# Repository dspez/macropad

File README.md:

Files sent to JLCPCB for macropad production - tested and functional

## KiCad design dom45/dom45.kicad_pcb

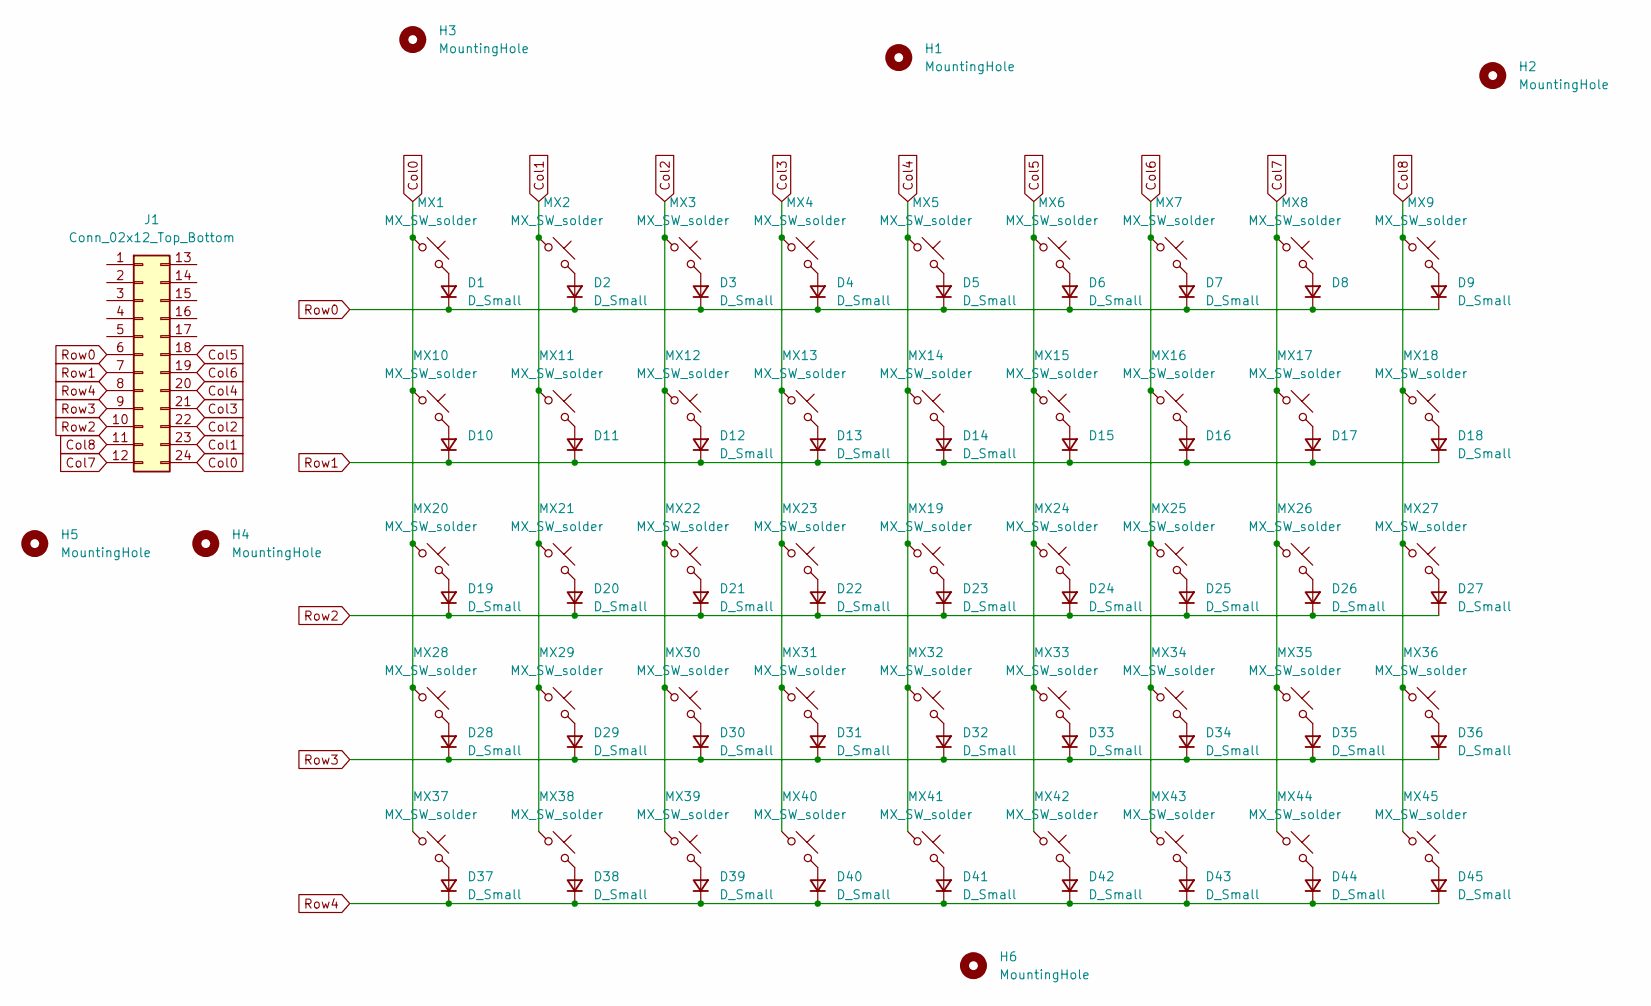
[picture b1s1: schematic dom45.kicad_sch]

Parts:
D1, D2, D3, D4, D5, D6, D7, D8, D9, D10, D11, D12, D13, D14, D15, D16, D17, D18, D19, D20, D21, D22, D23, D24, D25, D26, D27, D28, D29, D30, D31, D32, D33, D34, D35, D36, D37, D38, D39, D40, D41, D42, D43, D44, D45: D_Small; D_SOD-123; LCSC C81598
H1, H2, H3, H4, H5, H6: MountingHole; MountingHole_3.2mm_M3_DIN965_Pad_TopBottom
J1: Conn_02x12_Top_Bottom; ProMicro_USBup
MX1, MX2, MX3, MX4, MX5, MX6, MX7, MX8, MX9, MX10, MX11, MX12, MX13, MX14, MX15, MX16, MX17, MX18, MX19, MX20, MX21, MX22, MX23, MX24, MX25, MX26, MX27, MX28, MX29, MX30, MX31, MX32, MX33, MX34, MX35, MX36, MX37, MX38, MX39, MX40, MX41, MX42, MX43, MX44, MX45: MX_SW_solder; SW_MX_1u

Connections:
Col0: J1.24, MX1.1, MX10.1, MX20.1, MX28.1, MX37.1
Col1: J1.23, MX2.1, MX11.1, MX21.1, MX29.1, MX38.1
Col2: J1.22, MX3.1, MX12.1, MX22.1, MX30.1, MX39.1
Col3: J1.21, MX4.1, MX13.1, MX23.1, MX31.1, MX40.1
Col4: J1.20, MX5.1, MX14.1, MX19.1, MX32.1, MX41.1
Col5: J1.18, MX6.1, MX15.1, MX24.1, MX33.1, MX42.1
Col6: J1.19, MX7.1, MX16.1, MX25.1, MX34.1, MX43.1
Col7: J1.12, MX8.1, MX17.1, MX26.1, MX35.1, MX44.1
Col8: J1.11, MX9.1, MX18.1, MX27.1, MX36.1, MX45.1
unnamed: D1.2 (A), MX1.2
unnamed: D2.2 (A), MX2.2
unnamed: D3.2 (A), MX3.2
unnamed: D4.2 (A), MX4.2
unnamed: D5.2 (A), MX5.2
unnamed: D6.2 (A), MX6.2
unnamed: D7.2 (A), MX7.2
unnamed: D8.2 (A), MX8.2
unnamed: D9.2 (A), MX9.2
unnamed: D10.2 (A), MX10.2
unnamed: D11.2 (A), MX11.2
unnamed: D12.2 (A), MX12.2
unnamed: D13.2 (A), MX13.2
unnamed: D14.2 (A), MX14.2
unnamed: D15.2 (A), MX15.2
unnamed: D16.2 (A), MX16.2
unnamed: D17.2 (A), MX17.2
unnamed: D18.2 (A), MX18.2
unnamed: D19.2 (A), MX20.2
unnamed: D20.2 (A), MX21.2
unnamed: D21.2 (A), MX22.2
unnamed: D22.2 (A), MX23.2
unnamed: D23.2 (A), MX19.2
unnamed: D24.2 (A), MX24.2
unnamed: D25.2 (A), MX25.2
unnamed: D26.2 (A), MX26.2
unnamed: D27.2 (A), MX27.2
unnamed: D28.2 (A), MX28.2
unnamed: D29.2 (A), MX29.2
unnamed: D30.2 (A), MX30.2
unnamed: D31.2 (A), MX31.2
unnamed: D32.2 (A), MX32.2
unnamed: D33.2 (A), MX33.2
unnamed: D34.2 (A), MX34.2
unnamed: D35.2 (A), MX35.2
unnamed: D36.2 (A), MX36.2
unnamed: D37.2 (A), MX37.2
unnamed: D38.2 (A), MX38.2
unnamed: D39.2 (A), MX39.2
unnamed: D40.2 (A), MX40.2
unnamed: D41.2 (A), MX41.2
unnamed: D42.2 (A), MX42.2
unnamed: D43.2 (A), MX43.2
unnamed: D44.2 (A), MX44.2
unnamed: D45.2 (A), MX45.2
Row0: D1.1 (K), D2.1 (K), D3.1 (K), D4.1 (K), D5.1 (K), D6.1 (K), D7.1 (K), D8.1 (K), D9.1 (K), J1.6
Row1: D10.1 (K), D11.1 (K), D12.1 (K), D13.1 (K), D14.1 (K), D15.1 (K), D16.1 (K), D17.1 (K), D18.1 (K), J1.7
Row2: D19.1 (K), D20.1 (K), D21.1 (K), D22.1 (K), D23.1 (K), D24.1 (K), D25.1 (K), D26.1 (K), D27.1 (K), J1.10
Row3: D28.1 (K), D29.1 (K), D30.1 (K), D31.1 (K), D32.1 (K), D33.1 (K), D34.1 (K), D35.1 (K), D36.1 (K), J1.9
Row4: D37.1 (K), D38.1 (K), D39.1 (K), D40.1 (K), D41.1 (K), D42.1 (K), D43.1 (K), D44.1 (K), D45.1 (K), J1.8

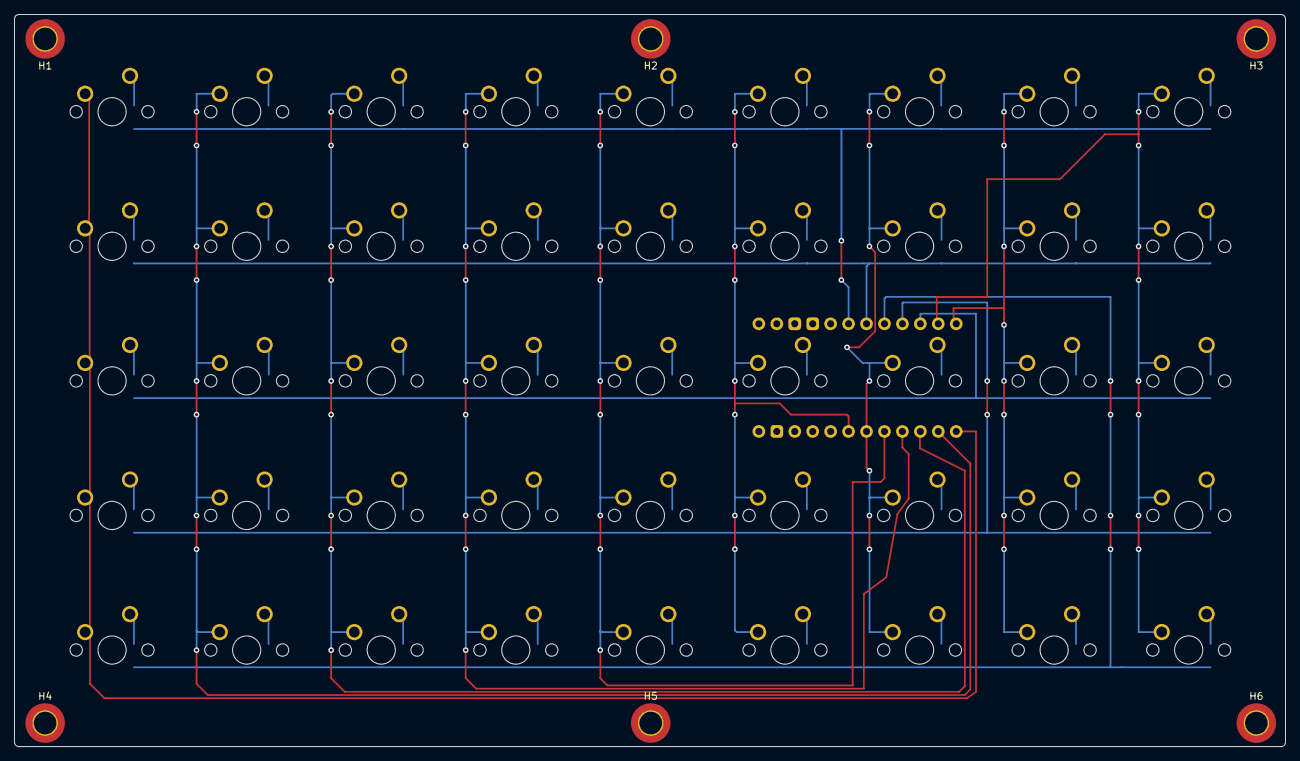
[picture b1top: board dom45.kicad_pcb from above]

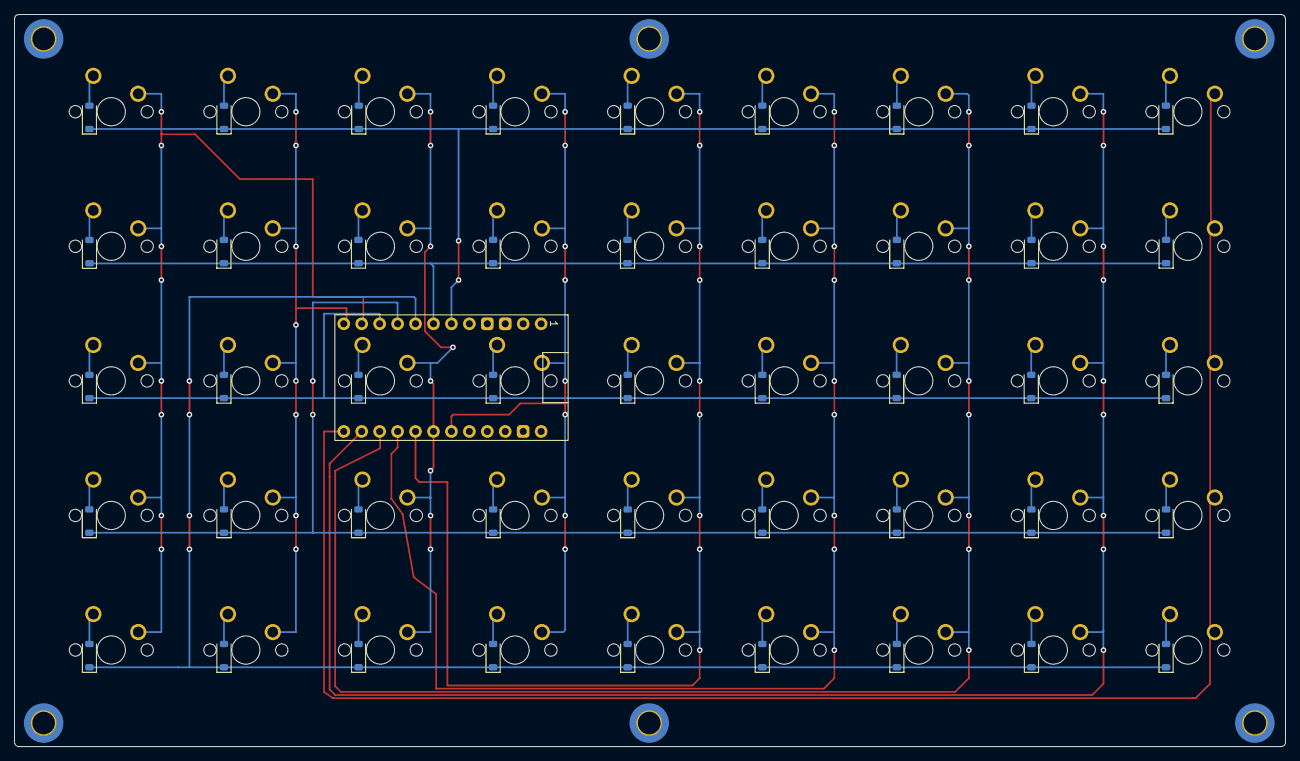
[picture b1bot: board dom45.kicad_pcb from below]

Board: 2 copper layers, 179.9 x 103.6 mm, 97 parts (46 on the bottom side), 59 nets.

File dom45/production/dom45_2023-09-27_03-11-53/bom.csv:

Designator,Footprint,Quantity,Value,LCSC Part #
"D1, D10, D11, D12, D13, D14, D15, D16, D17, D18, D19, D2, D20, D21, D22, D23, D24, D25, D26, D27, D28, D29, D3, D30, D31, D32, D33, D34, D35, D36, D37, D38, D39, D4, D40, D41, D42, D43, D44, D45, D5, D6, D7, D8, D9",D_SOD-123,45,D_Small,C81598
"H1, H2, H3, H4, H5, H6",MountingHole_3.2mm_M3_DIN965_Pad_TopBottom,6,MountingHole,
J1,ProMicro_USBup,1,Conn_02x12_Top_Bottom,
"MX1, MX10, MX11, MX12, MX13, MX14, MX15, MX16, MX17, MX18, MX19, MX2, MX20, MX21, MX22, MX23, MX24, MX25, MX26, MX27, MX28, MX29, MX3, MX30, MX31, MX32, MX33, MX34, MX35, MX36, MX37, MX38, MX39, MX4, MX40, MX41, MX42, MX43, MX44, MX45, MX5, MX6, MX7, MX8, MX9",SW_MX_1u,45,MX_SW_solder,

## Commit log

2023-01-01 First file
2023-01-01 add submodules
